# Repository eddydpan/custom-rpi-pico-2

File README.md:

# Custom RPi Pico 2
Eddy Pan

A custom RP2354A development board in the style of the Raspberry Pi Pico 2, designed in KiCad 10.

<p align="center">
  
  <br>
  <em>3D render</em>
</p>

<table align="center">
  <tr>
    <td align="center">
      
    </td>
    <td align="center">
      
    </td>
  </tr>
  <tr>
    <td align="center"><em>PCB layout</em></td>
    <td align="center"><em>Blinky on the user LED at 1 Hz</em> (<a href="assets/blinking.mp4">full video</a>)</td>
  </tr>
</table>

## Docs

`docs/` holds the schematic PDF, BoM, and board design submission.

## Firmware

### Dependencies (Fedora 44)

```sh
sudo dnf install cmake git python3 gcc-c++ libusb1-devel \
    arm-none-eabi-gcc-cs arm-none-eabi-gcc-cs-c++ arm-none-eabi-newlib
```

Clone the [Pico SDK](https://github.com/raspberrypi/pico-sdk) (this project used v2.3.1) into `/opt`. `CMakeLists.txt` expects it at `/opt/pico-sdk`:

```sh
sudo git clone https://github.com/raspberrypi/pico-sdk.git /opt/pico-sdk
sudo chown -R $USER: /opt/pico-sdk
cd /opt/pico-sdk && git submodule update --init
```

Build and install `picotool` (version must match the SDK) and its udev rules, so you can flash without `sudo`.
It needs `libusb1-devel` to talk to the board over USB; without it, picotool builds but can't flash.

```sh
sudo git clone --branch 2.3.1 https://github.com/raspberrypi/picotool.git /opt/picotool
sudo chown -R $USER: /opt/picotool
cmake -S /opt/picotool -B /opt/picotool/build -DPICO_SDK_PATH=/opt/pico-sdk
cmake --build /opt/picotool/build -j
sudo cmake --install /opt/picotool/build        # -> /usr/local/bin/picotool
sudo cp /opt/picotool/udev/60-picotool.rules /etc/udev/rules.d/
sudo udevadm control --reload && sudo udevadm trigger
```

If picotool isn't installed, the SDK downloads and builds a copy into `build/_deps/picotool/` instead.

### Project layout

- `CMakeLists.txt` – targets the RP2350 and our custom board, builds `blink`
- `boards/custom_pico2.h` – board definition (based on `pico2.h`, 2 MB flash, LED on GPIO 19)
- `src/blink.c` – blinks the user LED on GPIO 19

### Build and flash

```sh
cmake -S . -B build
cmake --build build -j
```

The first time (or if the board is running firmware without USB stdio), hold BOOTSEL while plugging in USB, then flash with picotool:

```sh
picotool load -x build/blink.uf2
```

(Alternatively, drag `build/blink.uf2` onto the `RP2350` drive.)

After that, firmware built with `pico_enable_stdio_usb` exposes a reset interface over USB, so picotool can reboot the board into BOOTSEL itself. No button needed:

```sh
picotool load -f -x build/blink.uf2
```

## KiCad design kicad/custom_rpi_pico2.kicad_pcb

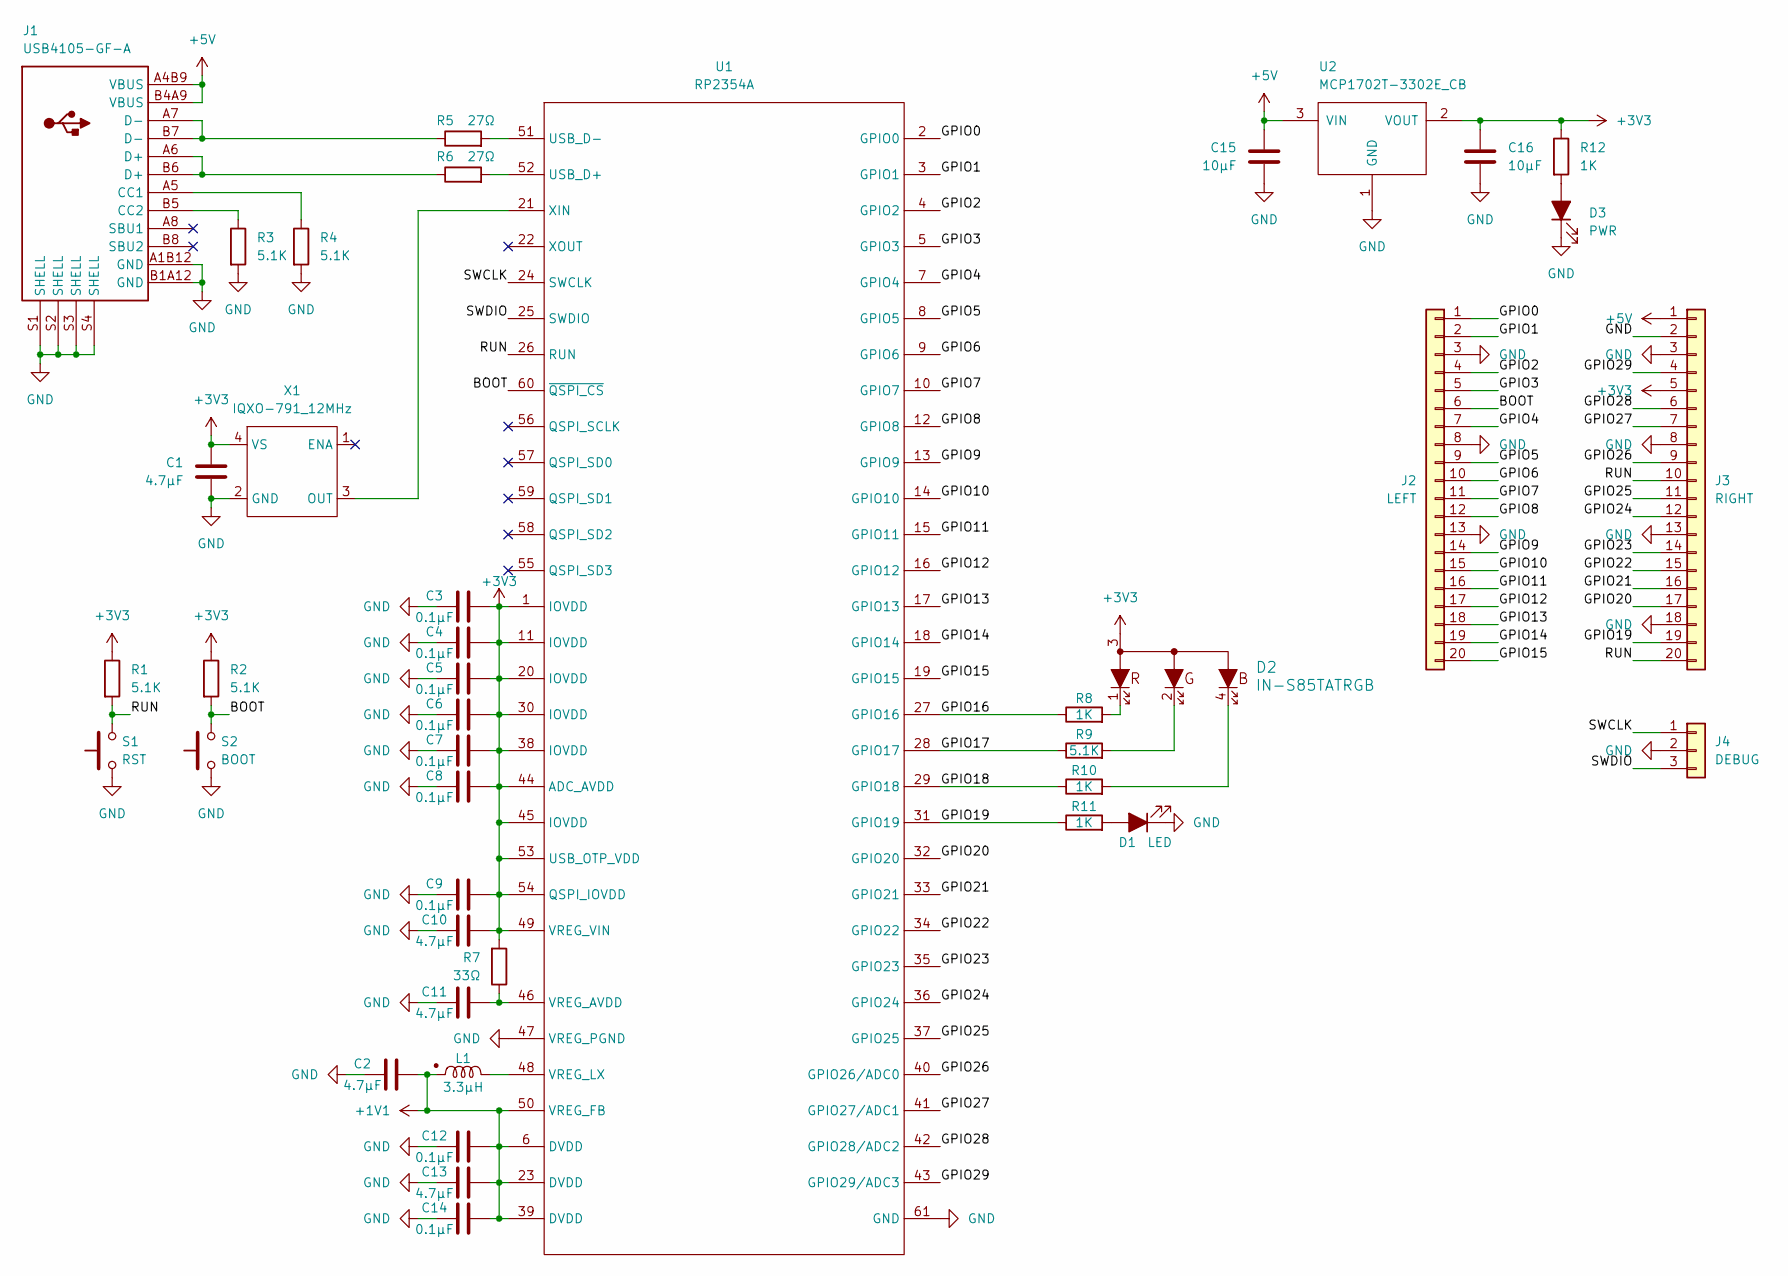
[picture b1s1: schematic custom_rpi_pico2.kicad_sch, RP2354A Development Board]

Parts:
C1, C11, C13: 4.7µF; C_0402_1005Metric
C2, C10: 4.7µF; R_0402_1005Metric
C3, C4, C5, C6, C7, C8, C9, C12, C14: 0.1µF; C_0402_1005Metric
C15, C16: 10µF; C_0603_1608Metric
D1: LED; LED_0805_2012Metric
D2: IN-S85TATRGB
D3: PWR; LED_0805_2012Metric
J1: USB4105-GF-A
J2: LEFT; PinHeader_1x20_P2.54mm_Vertical
J3: RIGHT; PinHeader_1x20_P2.54mm_Vertical
J4: DEBUG; PinHeader_1x03_P2.54mm_Vertical
L1: 3.3µH; AOTA-B201610S3R3-101-T
R1, R2, R3, R4, R9: 5.1K; R_0402_1005Metric
R5, R6: 27Ω; R_0402_1005Metric
R7: 33Ω; R_0402_1005Metric
R8, R10, R11, R12: 1K; R_0402_1005Metric
S1: RST; SW_SPST_B3U-1000P
S2: BOOT; SW_SPST_B3U-1000P
U1: RP2354A; RP2350A_QFN-60_EP_7.75x7.75_Pitch0.4mm
U2: MCP1702T-3302E_CB; SOT-23-3
X1: IQXO-791_12MHz; IQXO-791

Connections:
+1V1: C2.2, C12.2, C13.2, C14.2, L1.1, U1.6 (DVDD), U1.23 (DVDD), U1.39 (DVDD), U1.50 (VREG_FB)
+3V3: C1.2, C3.2, C4.2, C5.2, C6.2, C7.2, C8.2, C9.2, C10.2, C16.1, D2.3, J3.5, R1.1, R2.1, R7.2, R12.1, U1.1 (IOVDD), U1.11 (IOVDD), U1.20 (IOVDD), U1.30 (IOVDD), U1.38 (IOVDD), U1.44 (ADC_AVDD), U1.45 (IOVDD), U1.49 (VREG_VIN), U1.53 (USB_OTP_VDD), U1.54 (QSPI_IOVDD), U2.2 (VOUT), X1.4 (VS)
+5V: C15.2, J1.A4B9 (VBUS), J1.B4A9 (VBUS), J3.1, U2.3 (VIN)
/BOOT: J2.6, R2.2, S2.2, U1.60 (~QSPI_CS)
/GPIO0: J2.1, U1.2 (GPIO0)
/GPIO1: J2.2, U1.3 (GPIO1)
/GPIO2: J2.4, U1.4 (GPIO2)
/GPIO3: J2.5, U1.5 (GPIO3)
/GPIO4: J2.7, U1.7 (GPIO4)
/GPIO5: J2.9, U1.8 (GPIO5)
/GPIO6: J2.10, U1.9 (GPIO6)
/GPIO7: J2.11, U1.10 (GPIO7)
/GPIO8: J2.12, U1.12 (GPIO8)
/GPIO9: J2.14, U1.13 (GPIO9)
/GPIO10: J2.15, U1.14 (GPIO10)
/GPIO11: J2.16, U1.15 (GPIO11)
/GPIO12: J2.17, U1.16 (GPIO12)
/GPIO13: J2.18, U1.17 (GPIO13)
/GPIO14: J2.19, U1.18 (GPIO14)
/GPIO15: J2.20, U1.19 (GPIO15)
/GPIO16: R8.1, U1.27 (GPIO16)
/GPIO17: R9.1, U1.28 (GPIO17)
/GPIO18: R10.1, U1.29 (GPIO18)
/GPIO19: J3.19, R11.1, U1.31 (GPIO19)
/GPIO20: J3.17, U1.32 (GPIO20)
/GPIO21: J3.16, U1.33 (GPIO21)
/GPIO22: J3.15, U1.34 (GPIO22)
/GPIO23: J3.14, U1.35 (GPIO23)
/GPIO24: J3.12, U1.36 (GPIO24)
/GPIO25: J3.11, U1.37 (GPIO25)
/GPIO26: J3.9, U1.40 (GPIO26/ADC0)
/GPIO27: J3.7, U1.41 (GPIO27/ADC1)
/GPIO28: J3.6, U1.42 (GPIO28/ADC2)
/GPIO29: J3.4, U1.43 (GPIO29/ADC3)
/RUN: J3.10, J3.20, R1.2, S1.2, U1.26 (RUN)
/SWCLK: J4.1, U1.24 (SWCLK)
/SWDIO: J4.3, U1.25 (SWDIO)
GND: C1.1, C2.1, C3.1, C4.1, C5.1, C6.1, C7.1, C8.1, C9.1, C10.1, C11.1, C12.1, C13.1, C14.1, C15.1, C16.2, D1.1 (K), D3.1 (K), J1.A1B12 (GND), J1.B1A12 (GND), J1.S1 (SHELL), J1.S2 (SHELL), J1.S3 (SHELL), J1.S4 (SHELL), J2.3, J2.8, J2.13, J3.2, J3.3, J3.8, J3.13, J3.18, J4.2, R3.2, R4.2, S1.1, S2.1, U1.47 (VREG_PGND), U1.61 (GND), U2.1 (GND), X1.2 (GND)
unnamed: D1.2 (A), R11.2
unnamed: D2.1, R8.2
unnamed: D2.2, R9.2
unnamed: D2.4, R10.2
unnamed: D3.2 (A), R12.2
unnamed: J1.A5 (CC1), R4.1
unnamed: J1.B5 (CC2), R3.1
unnamed: J1.A6 (D+), J1.B6 (D+), R6.1
unnamed: J1.A7 (D-), J1.B7 (D-), R5.1
unnamed: R6.2, U1.52 (USB_D+)
unnamed: R5.2, U1.51 (USB_D-)
unnamed: C11.2, R7.1, U1.46 (VREG_AVDD)
unnamed: L1.2, U1.48 (VREG_LX)
unnamed: U1.21 (XIN), X1.3 (OUT)

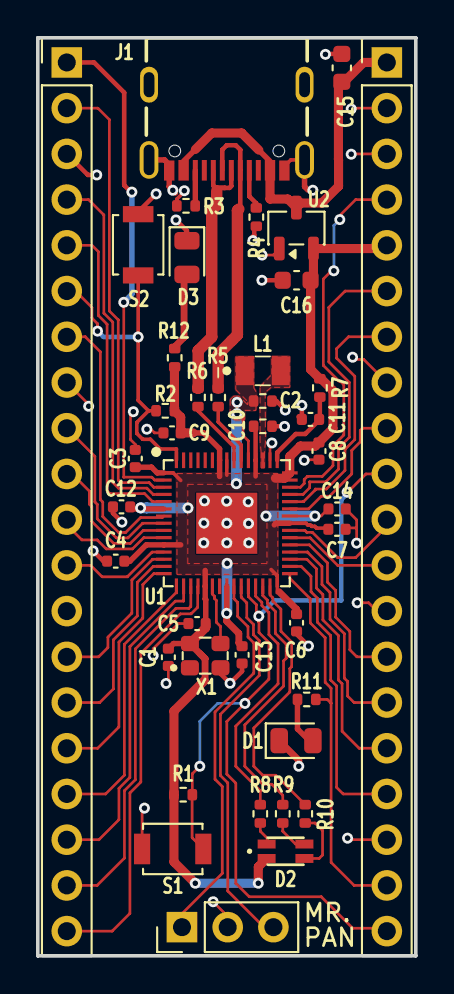
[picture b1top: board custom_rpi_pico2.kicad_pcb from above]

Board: 2 copper layers, 21.0 x 51.0 mm, 41 parts (0 on the bottom side), 52 nets.
